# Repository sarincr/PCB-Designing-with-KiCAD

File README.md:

# PCB-Designing-with-KiCAD
KiCad is a free software suite for electronic design automation. It facilitates the design of schematics for electronic circuits and their conversion to PCB designs. KiCad was originally developed by Jean-Pierre Charras. It features an integrated environment for schematic capture and PCB layout design.

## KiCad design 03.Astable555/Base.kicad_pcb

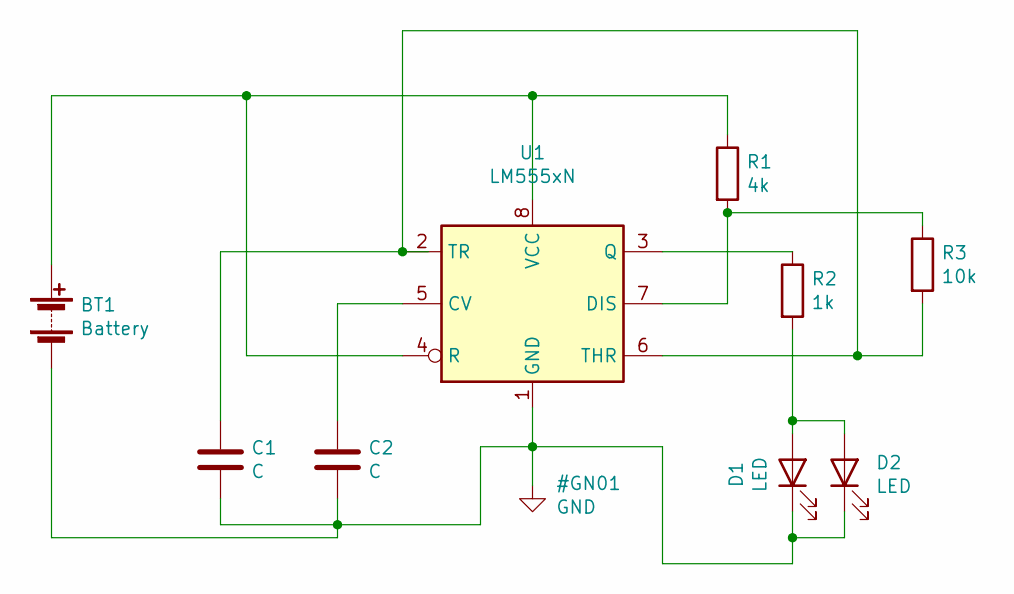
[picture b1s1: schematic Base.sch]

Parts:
BT1: Battery; BatteryHolder_Bulgin_BX0036_1xC
C1, C2: C; CP_Axial_L10.0mm_D4.5mm_P15.00mm_Horizontal
D1, D2: LED; LED_BL-FL7680RGB
R1: 4k; R_Axial_DIN0204_L3.6mm_D1.6mm_P1.90mm_Vertical
R2: 1k; R_Axial_DIN0204_L3.6mm_D1.6mm_P1.90mm_Vertical
R3: 10k; R_Axial_DIN0204_L3.6mm_D1.6mm_P1.90mm_Vertical
U1: LM555xN; DIP-8_W7.62mm

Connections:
GND: BT1.2 (-), C1.2, C2.2, D1.1 (K), D2.1 (K), U1.1 (GND)
unnamed: BT1.1 (+), R1.1, U1.4 (R), U1.8 (VCC)
unnamed: C1.1, R3.2, U1.2 (TR), U1.6 (THR)
unnamed: C2.1, U1.5 (CV)
unnamed: D1.2 (A), D2.2 (A), R2.2
unnamed: R1.2, R3.1, U1.7 (DIS)
unnamed: R2.1, U1.3 (Q)

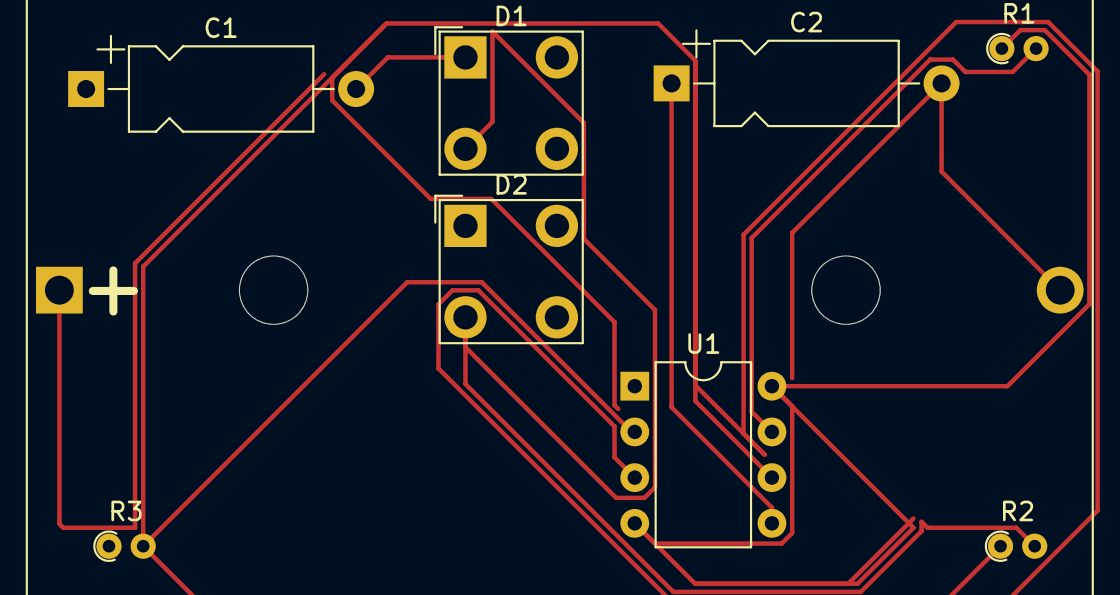
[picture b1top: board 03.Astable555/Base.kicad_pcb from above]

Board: 2 copper layers, 9 parts (0 on the bottom side), 7 nets.

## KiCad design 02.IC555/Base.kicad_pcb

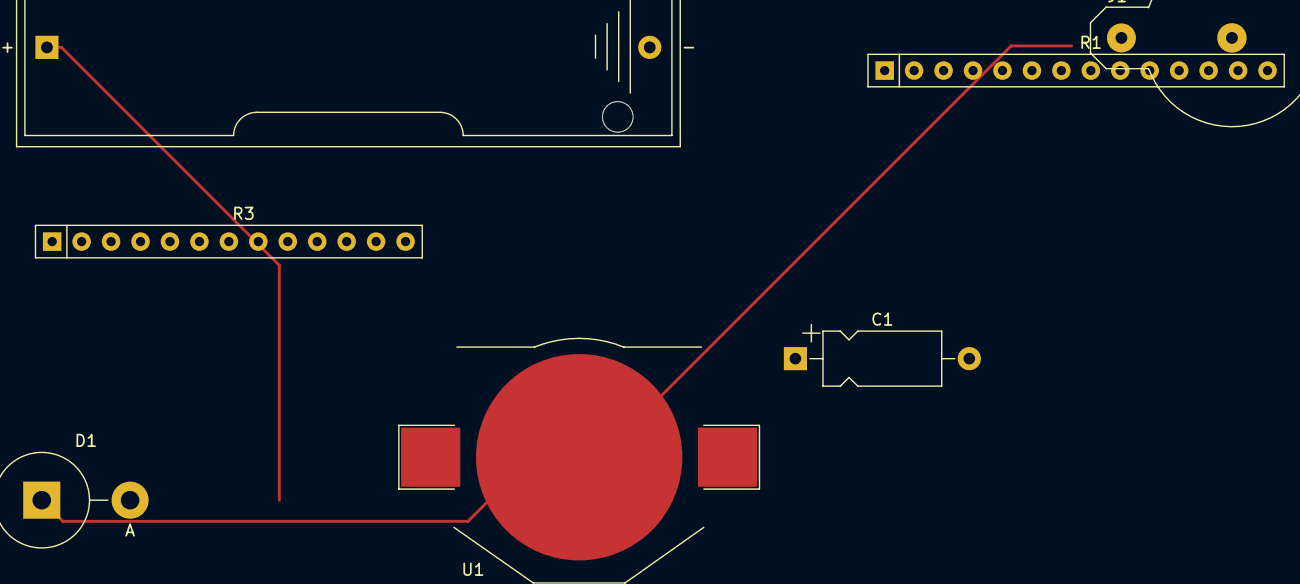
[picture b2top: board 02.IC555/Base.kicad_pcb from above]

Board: 2 copper layers, 7 parts (0 on the bottom side), 5 nets.

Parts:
C1: 1Uf; CP_Axial_L10.0mm_D4.5mm_P15.00mm_Horizontal
D1: LED; D_5KPW_P7.62mm_Vertical_AnodeUp
J1: IN; BatteryHolder_Keystone_500
R1: 1K; R_Array_SIP14
R2: 470; BatteryHolder_Keystone_2460_1xAA
R3: 1K; R_Array_SIP13
U1: LM555xMM; BatteryHolder_Keystone_3002_1x2032

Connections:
1: R1.2, R3.1
+2V5: J1.2, R1.1
unnamed: C1.1, R3.2, U1.2
unnamed: C1.2, D1.1, J1.1, U1.1
unnamed: D1.2, R2.1

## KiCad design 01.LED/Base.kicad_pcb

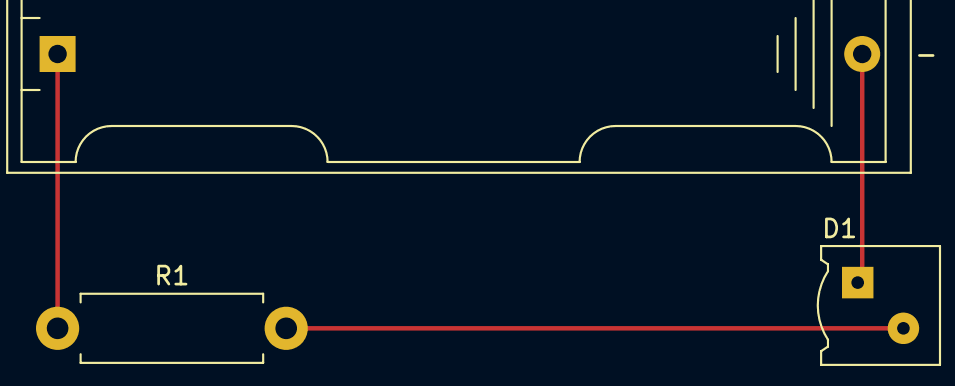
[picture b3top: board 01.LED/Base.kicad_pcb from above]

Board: 2 copper layers, 3 parts (0 on the bottom side), 3 nets.

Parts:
BT1: 5V; BatteryHolder_Keystone_2466_1xAAA
D1: LED; LED_VCCLite_5381H7_6.35x6.35mm
R1: 470; R_Axial_DIN0411_L9.9mm_D3.6mm_P12.70mm_Horizontal

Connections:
unnamed: BT1.1, R1.1
unnamed: BT1.2, D1.1
unnamed: D1.2, R1.2

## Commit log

2021-09-03 IC 555
2021-09-03 Base
